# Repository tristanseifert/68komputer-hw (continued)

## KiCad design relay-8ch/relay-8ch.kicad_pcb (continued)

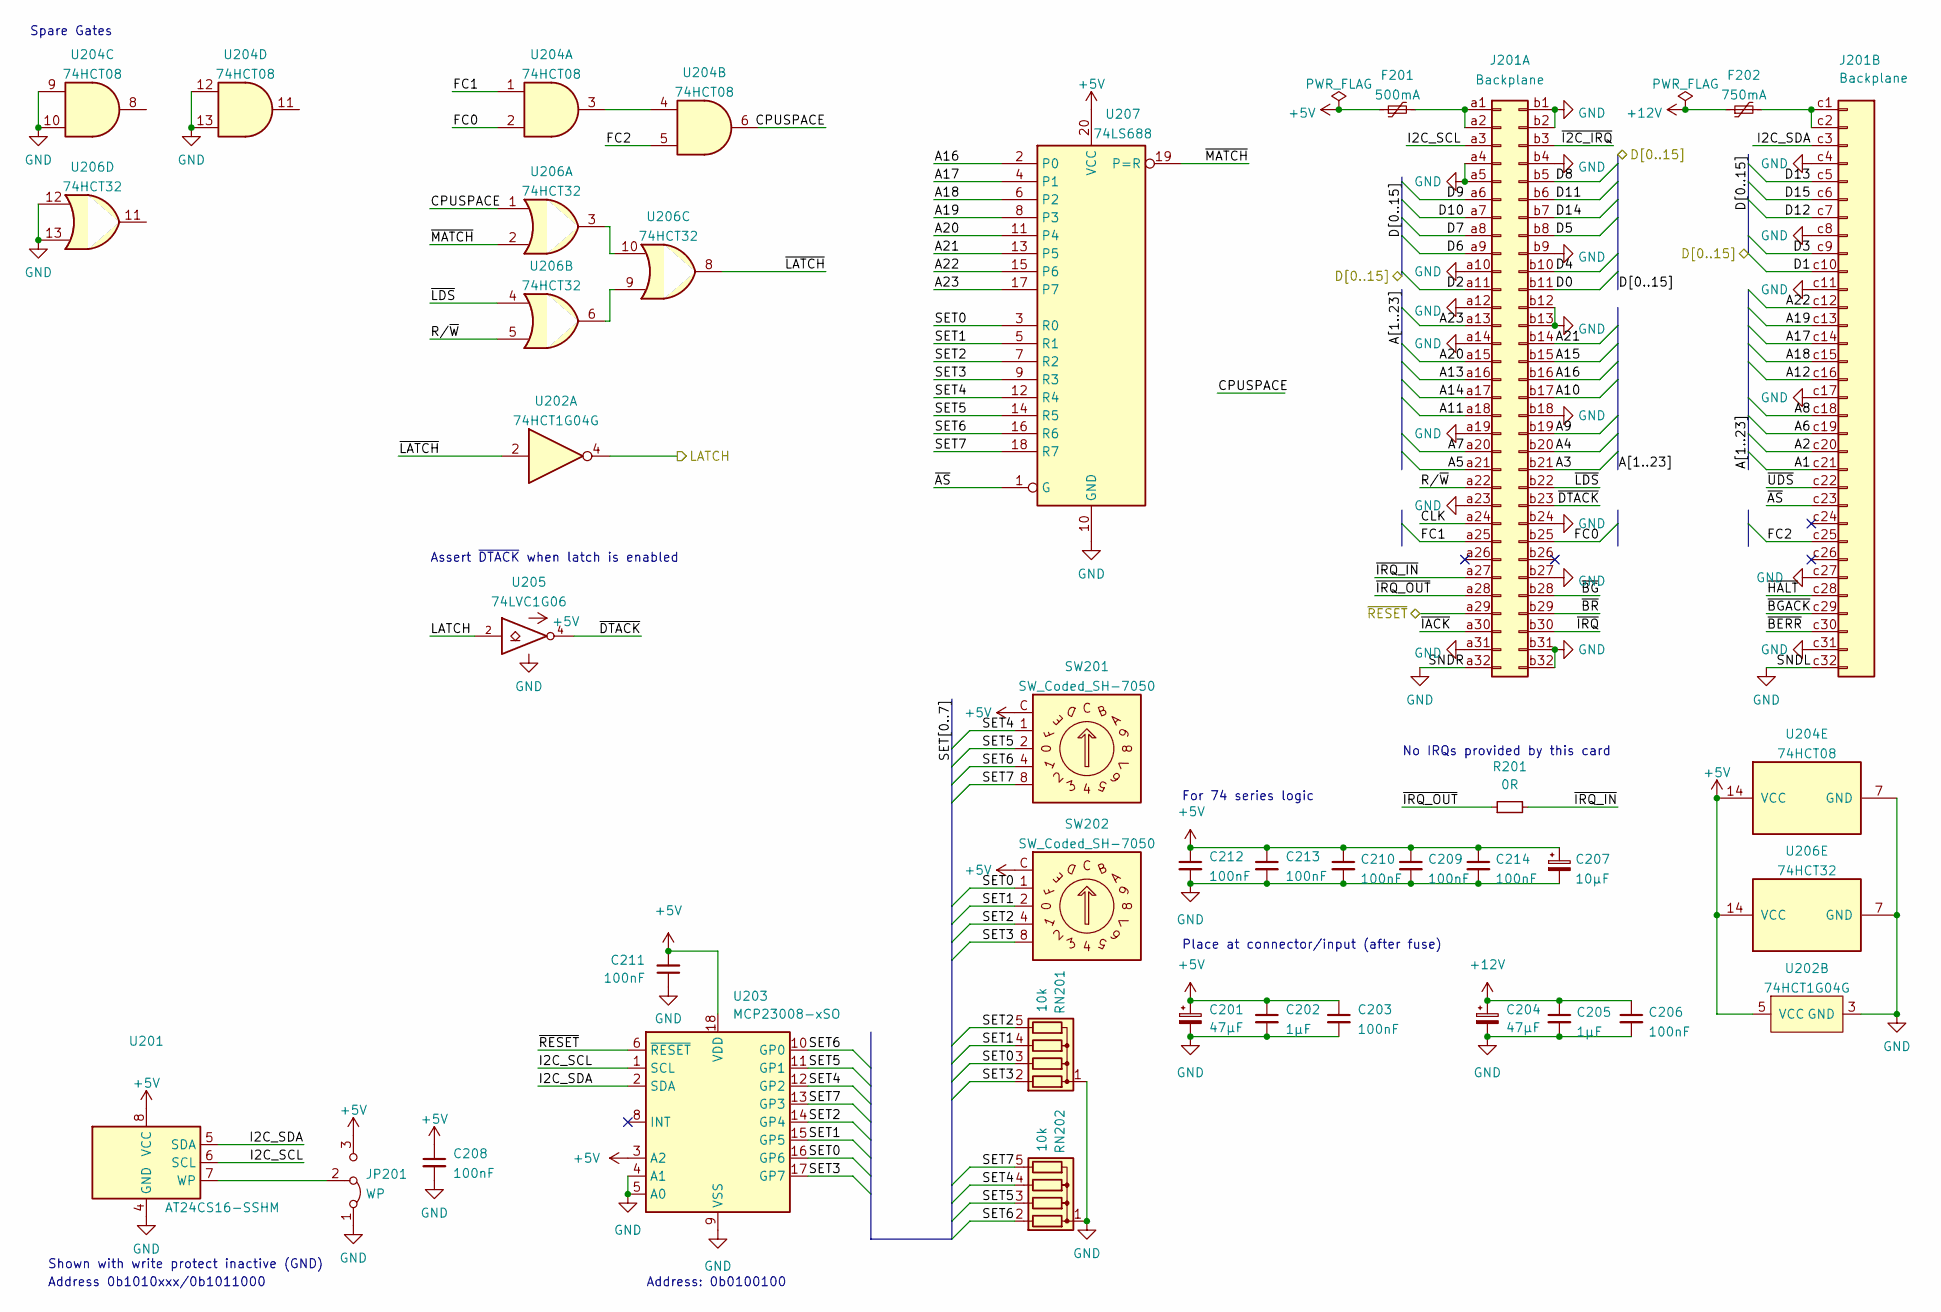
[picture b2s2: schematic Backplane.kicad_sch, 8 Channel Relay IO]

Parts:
C201, C204: 47µF; CP_Elec_6.3x5.7; MPN A768EB476M1ELAS042
C202, C205: 1µF; C_0805_2012Metric
C203, C206, C208, C209, C210, C211, C212, C213, C214: 100nF; C_0805_2012Metric
C207: 10µF; CP_EIA-3216-18_Kemet-A; MPN TAJA106K016RNJV
F201: 500mA; Fuse_1812_4532Metric; MPN 0ZCG0050FF2C
F202: 750mA; Fuse_1812_4532Metric; MPN 0ZCG0075FF2C
J201: Backplane; DIN41612_R_3x32_Male_Horizontal_THT
JP201: WP; SolderJumper-3_P1.3mm_Bridged2Bar12_Pad1.0x1.5mm
R201: 0R; R_0805_2012Metric; MPN RC0805JR-100RL
RN201, RN202: 10k; R_Array_SIP5; MPN 4605X-101-103LF
SW201, SW202: SW_Coded_SH-7050; Nidec_Copal_SH-7010C; MPN SH-7050MC
U201: AT24CS16-SSHM; SOIC-8_3.9x4.9mm_P1.27mm; MPN AT24CS32-SSHM-T
U202: 74HCT1G04G; SC-74-5_1.5x2.9mm_P0.95mm
U203: MCP23008-xSO; SOIC-18W_7.5x11.6mm_P1.27mm
U204: 74HCT08; SO-14_3.9x8.65mm_P1.27mm
U205: 74LVC1G06; SC-74-5_1.5x2.9mm_P0.95mm; MPN 74LVC1G06GV,125
U206: 74HCT32; SO-14_3.9x8.65mm_P1.27mm
U207: 74LS688; SOIC-20W_7.5x12.8mm_P1.27mm; MPN SN74LS688DWR

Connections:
+5V: C201.1, C202.1, C203.1, C207.1, C208.1, C209.1, C210.1, C211.2, C212.1, C213.1, C214.1, F201.1, JP201.3 (B), SW201.C, SW202.C, U201.8 (VCC), U202.5 (VCC), U203.3 (A2), U203.18 (VDD), U204.14 (VCC), U205.5 (VCC), U206.14 (VCC), U207.20 (VCC); also elsewhere on the board
+12V: C204.1, C205.1, C206.1, F202.1; also elsewhere on the board
/Backplane Connection/A1: J201.c21
/Backplane Connection/A2: J201.c20
/Backplane Connection/A3: J201.b21
/Backplane Connection/A4: J201.b20
/Backplane Connection/A5: J201.a21
/Backplane Connection/A6: J201.c19
/Backplane Connection/A7: J201.a20
/Backplane Connection/A8: J201.c18
/Backplane Connection/A9: J201.b19
/Backplane Connection/A10: J201.b17
/Backplane Connection/A11: J201.a18
/Backplane Connection/A12: J201.c16
/Backplane Connection/A13: J201.a16
/Backplane Connection/A14: J201.a17
/Backplane Connection/A15: J201.b15
/Backplane Connection/A16: J201.b16, U207.2 (P0)
/Backplane Connection/A17: J201.c14, U207.4 (P1)
/Backplane Connection/A18: J201.c15, U207.6 (P2)
/Backplane Connection/A19: J201.c13, U207.8 (P3)
/Backplane Connection/A20: J201.a15, U207.11 (P4)
/Backplane Connection/A21: J201.b14, U207.13 (P5)
/Backplane Connection/A22: J201.c12, U207.15 (P6)
/Backplane Connection/A23: J201.a13, U207.17 (P7)
/Backplane Connection/CLK: J201.a24
/Backplane Connection/CPUSPACE: U204.6, U206.1
/Backplane Connection/D8: J201.b5
/Backplane Connection/D9: J201.a6
/Backplane Connection/D10: J201.a7
/Backplane Connection/D11: J201.b6
/Backplane Connection/D12: J201.c7
/Backplane Connection/D13: J201.c5
/Backplane Connection/D14: J201.b7
/Backplane Connection/D15: J201.c6
/Backplane Connection/FC0: J201.b25, U204.2
/Backplane Connection/FC1: J201.a25, U204.1
/Backplane Connection/FC2: J201.c25, U204.5
/Backplane Connection/I2C_SCL: J201.a3, U201.6 (SCL), U203.1 (SCL)
/Backplane Connection/I2C_SDA: J201.c3, U201.5 (SDA), U203.2 (SDA)
/Backplane Connection/R/~W: J201.a22, U206.5
/Backplane Connection/SET0: RN201.3 (R2), SW202.1, U203.16 (GP6), U207.3 (R0)
/Backplane Connection/SET1: RN201.4 (R3), SW202.2, U203.15 (GP5), U207.5 (R1)
/Backplane Connection/SET2: RN201.5 (R4), SW202.4, U203.14 (GP4), U207.7 (R2)
/Backplane Connection/SET3: RN201.2 (R1), SW202.8, U203.17 (GP7), U207.9 (R3)
/Backplane Connection/SET4: RN202.4 (R3), SW201.1, U203.12 (GP2), U207.12 (R4)
/Backplane Connection/SET5: RN202.3 (R2), SW201.2, U203.11 (GP1), U207.14 (R5)
/Backplane Connection/SET6: RN202.2 (R1), SW201.4, U203.10 (GP0), U207.16 (R6)
/Backplane Connection/SET7: RN202.5 (R4), SW201.8, U203.13 (GP3), U207.18 (R7)
/Backplane Connection/~AS: J201.c23, U207.1 (G)
/Backplane Connection/~BERR: J201.c30
/Backplane Connection/~BGACK: J201.c29
/Backplane Connection/~BG: J201.b28
/Backplane Connection/~BR: J201.b29
/Backplane Connection/~DTACK: J201.b23, U205.4
/Backplane Connection/~HALT: J201.c28
/Backplane Connection/~I2C_IRQ: J201.b3
/Backplane Connection/~IACK: J201.a30
/Backplane Connection/~IRQ_IN: J201.a27, R201.2
/Backplane Connection/~IRQ_OUT: J201.a28, R201.1
/Backplane Connection/~IRQ: J201.b30
/Backplane Connection/~LATCH: U202.2, U206.8
/Backplane Connection/~LDS: J201.b22, U206.4
/Backplane Connection/~MATCH: U206.2, U207.19 (P=R)
/Backplane Connection/~RESET: J201.a29, U203.6 (~RESET)
/Backplane Connection/~UDS: J201.c22
/D0: J201.b11; also elsewhere on the board
/D1: J201.c10; also elsewhere on the board
/D2: J201.a11; also elsewhere on the board
/D3: J201.c9; also elsewhere on the board
/D4: J201.b10; also elsewhere on the board
/D5: J201.b8; also elsewhere on the board
/D6: J201.a9; also elsewhere on the board
/D7: J201.a8; also elsewhere on the board
/LATCH: U202.4, U205.2; also elsewhere on the board
GND: C201.2, C202.2, C203.2, C204.2, C205.2, C206.2, C207.2, C208.2, C209.2, C210.2, C211.1, C212.2, C213.2, C214.2, J201.a4, J201.a5, J201.a10, J201.a12, J201.a14, J201.a19, J201.a23, J201.a31, J201.a32, J201.b1, J201.b2, J201.b4, J201.b9, J201.b12, J201.b13, J201.b18, J201.b24, J201.b27, J201.b31, J201.b32, J201.c4, J201.c8, J201.c11, J201.c17, J201.c27, J201.c31, J201.c32, JP201.1 (A), RN201.1 (common), RN202.1 (common), U201.4 (GND), U202.3 (GND), U203.4 (A1), U203.5 (A0), U203.9 (VSS), U204.7 (GND), U204.9, U204.10, U204.12, U204.13, U205.3 (GND), U206.7 (GND), U206.12, U206.13, U207.10 (GND); also elsewhere on the board
unnamed: F201.2, J201.a1, J201.a2
unnamed: F202.2, J201.c1, J201.c2
unnamed: JP201.2 (C), U201.7 (WP)
unnamed: U204.3, U204.4
unnamed: U206.6, U206.9
unnamed: U206.3, U206.10

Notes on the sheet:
Shown with write protect inactive (GND)
Place at connector/input (after fuse)
No IRQs provided by this card
Spare Gates
Assert ~{DTACK} when latch is enabled
For 74 series logic
Address 0b1010xxx/0b1011000
Address: 0b0100100

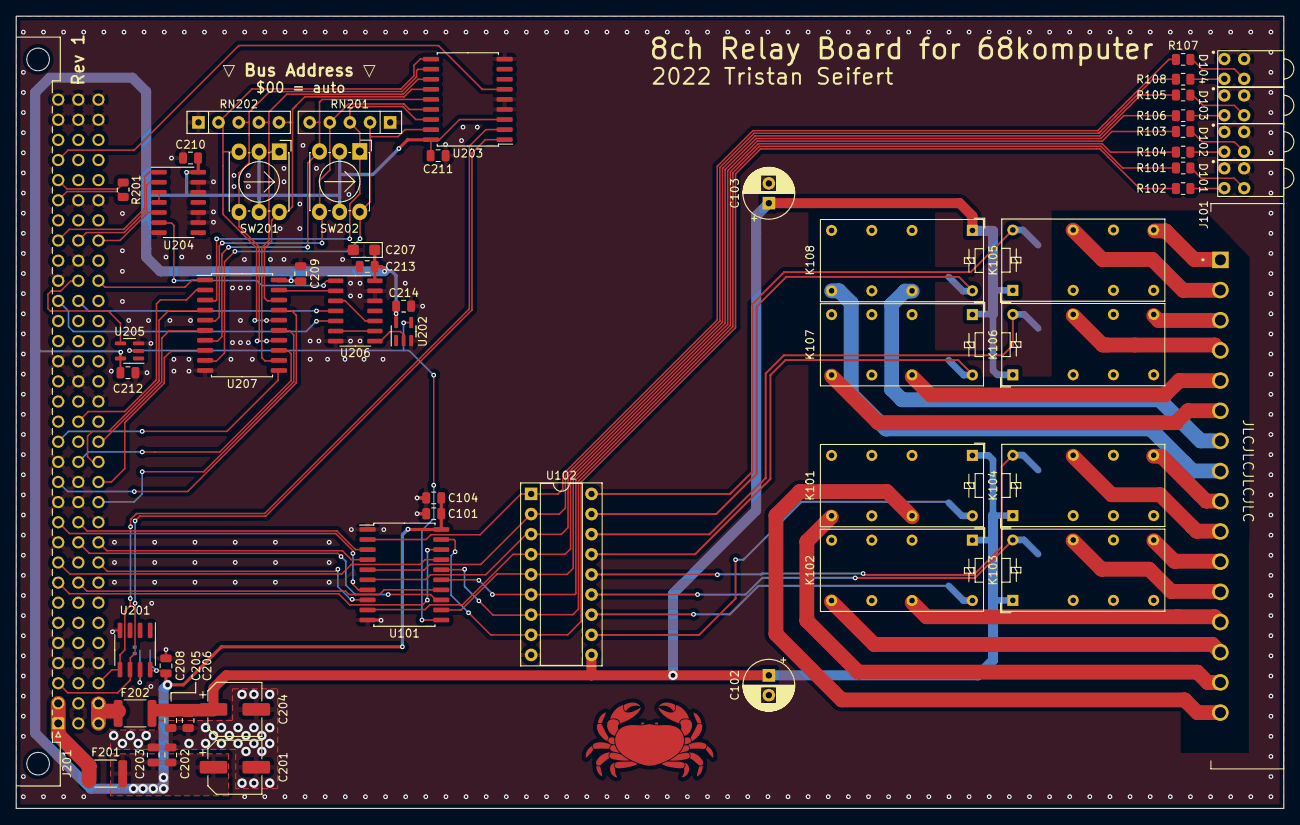
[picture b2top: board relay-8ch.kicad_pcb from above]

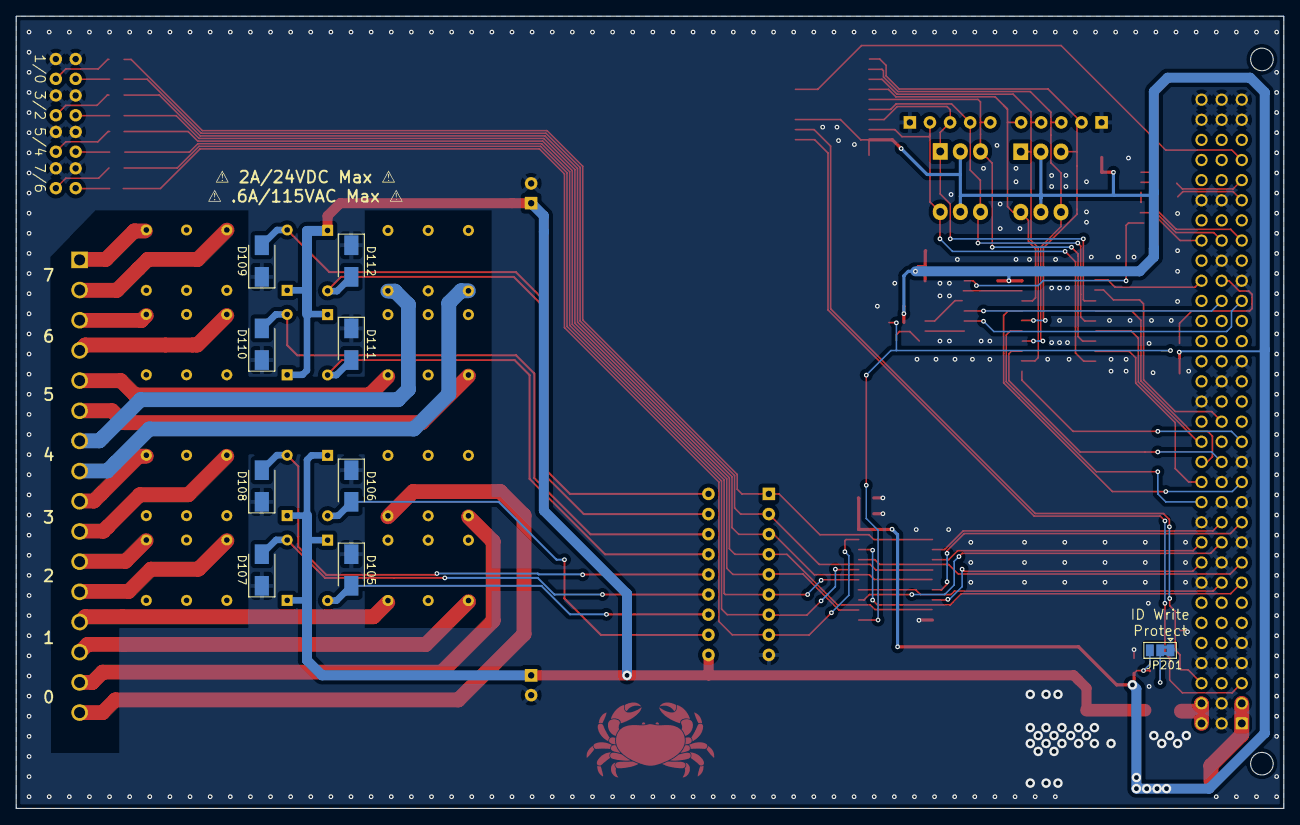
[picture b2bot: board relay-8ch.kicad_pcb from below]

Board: 2 copper layers, 160.0 x 100.0 mm, 65 parts (9 on the bottom side), 89 nets.

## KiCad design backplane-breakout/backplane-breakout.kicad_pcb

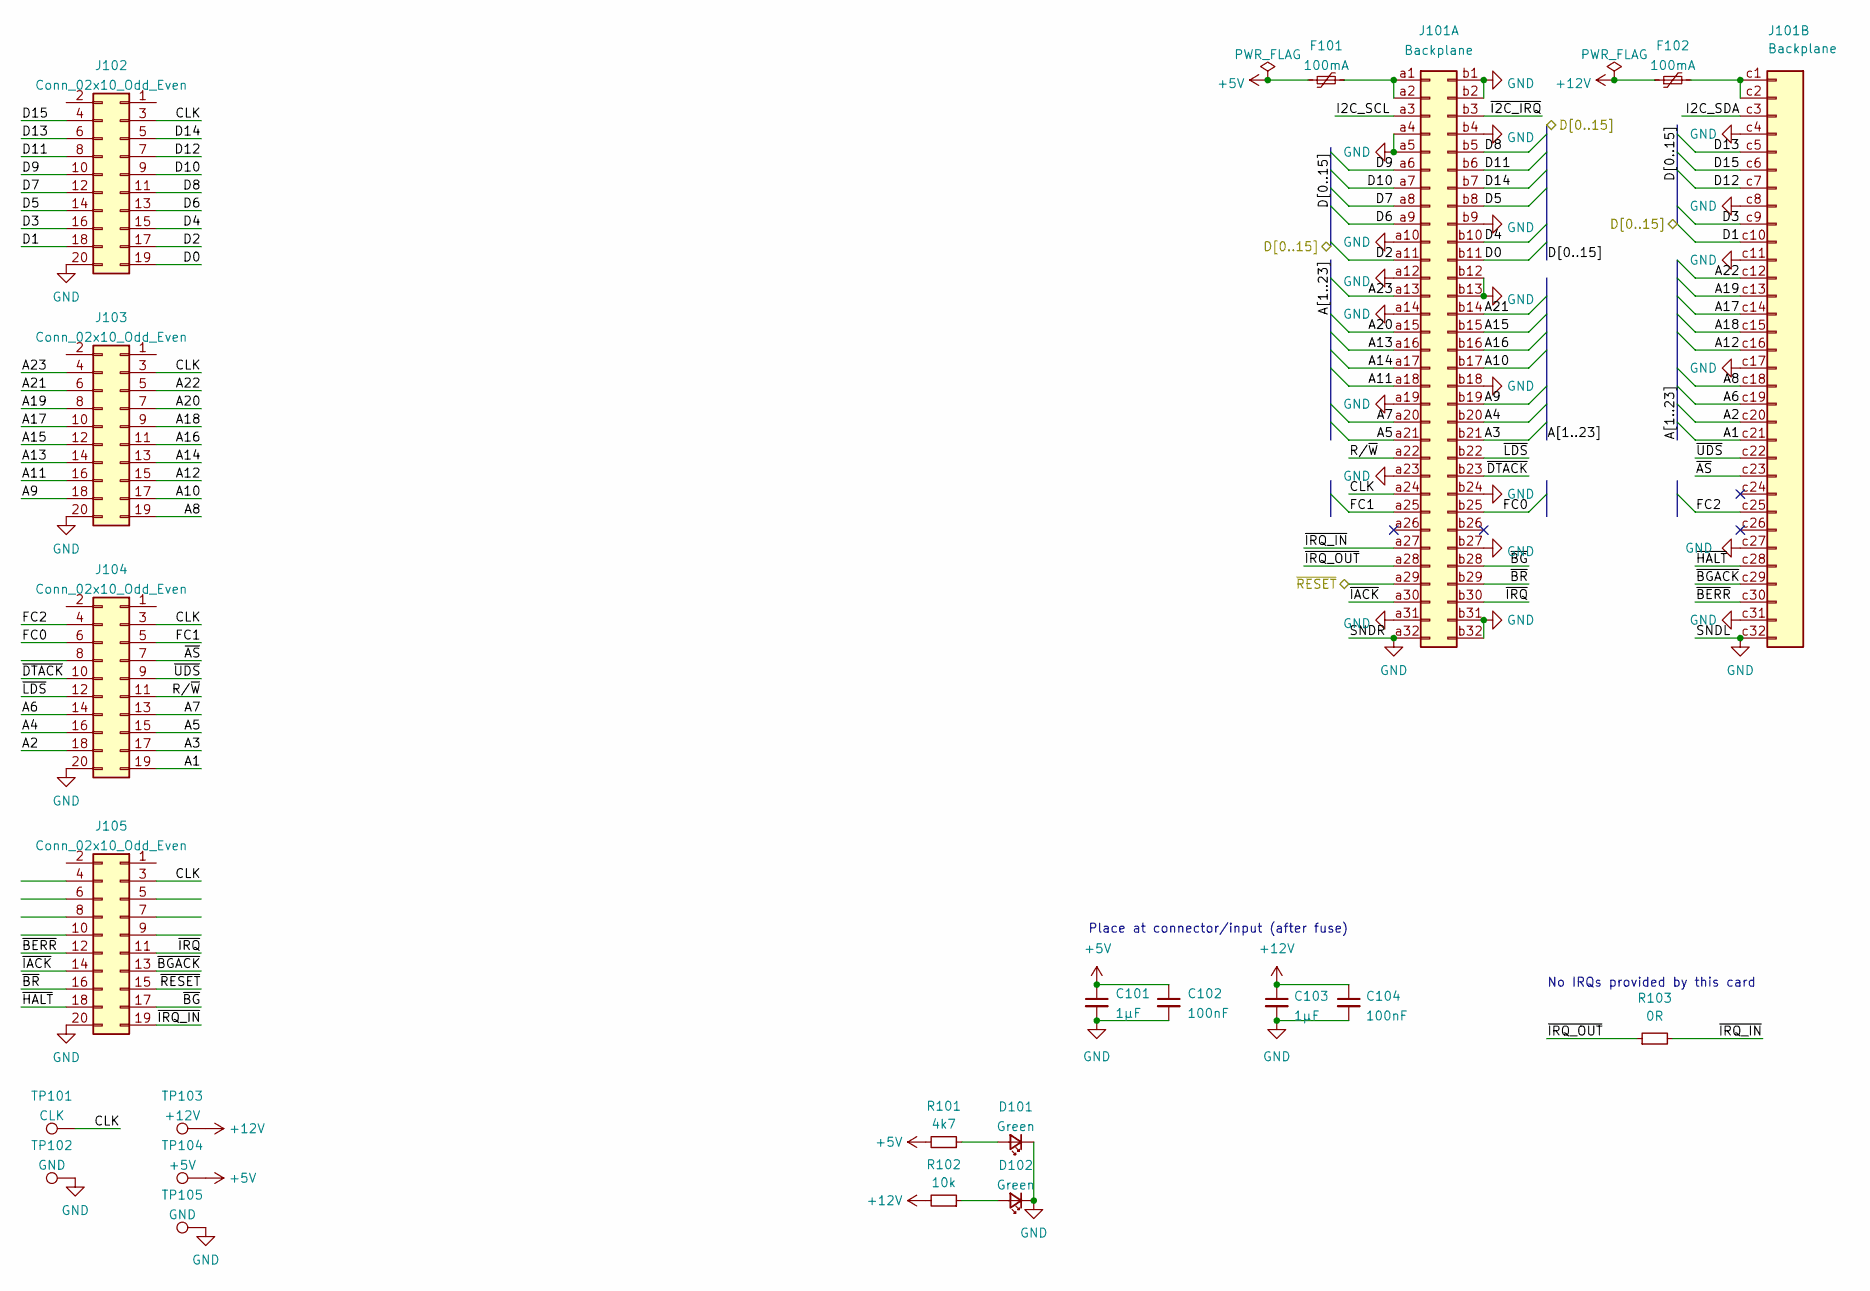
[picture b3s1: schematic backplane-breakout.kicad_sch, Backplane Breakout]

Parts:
C101, C103: 1µF; C_0805_2012Metric
C102, C104: 100nF; C_0805_2012Metric
D101, D102: Green; LED_0805_2012Metric
F101, F102: 100mA; Fuse_1812_4532Metric; MPN PTS181230V010
J101: Backplane; DIN41612_R_3x32_Male_Horizontal_THT; MPN 86093967113H55ELF
J102, J103, J104, J105: Conn_02x10_Odd_Even; Shrouded_PinHeader_2x10_P2.54mm_Vertical
R101: 4k7; R_0805_2012Metric
R102: 10k; R_0805_2012Metric
R103: 0R; R_0805_2012Metric; MPN RC0805JR-100RL
TP101: CLK; TestPoint_Keystone_5000-5004_Miniature
TP102, TP105: GND; TestPoint_Keystone_5000-5004_Miniature
TP103: +12V; TestPoint_Keystone_5000-5004_Miniature
TP104: +5V; TestPoint_Keystone_5000-5004_Miniature

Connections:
+5V: C101.1, C102.1, F101.1, R101.2, TP104.1
+12V: C103.1, C104.1, F102.1, R102.2, TP103.1
/A1: J101.c21, J104.19
/A2: J101.c20, J104.18
/A3: J101.b21, J104.17
/A4: J101.b20, J104.16
/A5: J101.a21, J104.15
/A6: J101.c19, J104.14
/A7: J101.a20, J104.13
/A8: J101.c18, J103.19
/A9: J101.b19, J103.18
/A10: J101.b17, J103.17
/A11: J101.a18, J103.16
/A12: J101.c16, J103.15
/A13: J101.a16, J103.14
/A14: J101.a17, J103.13
/A15: J101.b15, J103.12
/A16: J101.b16, J103.11
/A17: J101.c14, J103.10
/A18: J101.c15, J103.9
/A19: J101.c13, J103.8
/A20: J101.a15, J103.7
/A21: J101.b14, J103.6
/A22: J101.c12, J103.5
/A23: J101.a13, J103.4
/CLK: J101.a24, J102.3, J103.3, J104.3, J105.3, TP101.1
/D0: J101.b11, J102.19
/D1: J101.c10, J102.18
/D2: J101.a11, J102.17
/D3: J101.c9, J102.16
/D4: J101.b10, J102.15
/D5: J101.b8, J102.14
/D6: J101.a9, J102.13
/D7: J101.a8, J102.12
/D8: J101.b5, J102.11
/D9: J101.a6, J102.10
/D10: J101.a7, J102.9
/D11: J101.b6, J102.8
/D12: J101.c7, J102.7
/D13: J101.c5, J102.6
/D14: J101.b7, J102.5
/D15: J101.c6, J102.4
/FC0: J101.b25, J104.6
/FC1: J101.a25, J104.5
/FC2: J101.c25, J104.4
/I2C_SCL: J101.a3
/I2C_SDA: J101.c3
/R/~W: J101.a22, J104.11
/~AS: J101.c23, J104.7
/~BERR: J101.c30, J105.12
/~BGACK: J101.c29, J105.13
/~BG: J101.b28, J105.17
/~BR: J101.b29, J105.16
/~DTACK: J101.b23, J104.10
/~HALT: J101.c28, J105.18
/~I2C_IRQ: J101.b3
/~IACK: J101.a30, J105.14
/~IRQ_IN: J101.a27, J105.19, R103.2
/~IRQ_OUT: J101.a28, R103.1
/~IRQ: J101.b30, J105.11
/~LDS: J101.b22, J104.12
/~RESET: J101.a29, J105.15
/~UDS: J101.c22, J104.9
GND: C101.2, C102.2, C103.2, C104.2, D101.1 (K), D102.1 (K), J101.a4, J101.a5, J101.a10, J101.a12, J101.a14, J101.a19, J101.a23, J101.a31, J101.a32, J101.b1, J101.b2, J101.b4, J101.b9, J101.b12, J101.b13, J101.b18, J101.b24, J101.b27, J101.b31, J101.b32, J101.c4, J101.c8, J101.c11, J101.c17, J101.c27, J101.c31, J101.c32, J102.20, J103.20, J104.20, J105.20, TP102.1, TP105.1
unnamed: D101.2 (A), R101.1
unnamed: D102.2 (A), R102.1
unnamed: F101.2, J101.a1, J101.a2
unnamed: F102.2, J101.c1, J101.c2

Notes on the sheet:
No IRQs provided by this card
Place at connector/input (after fuse)

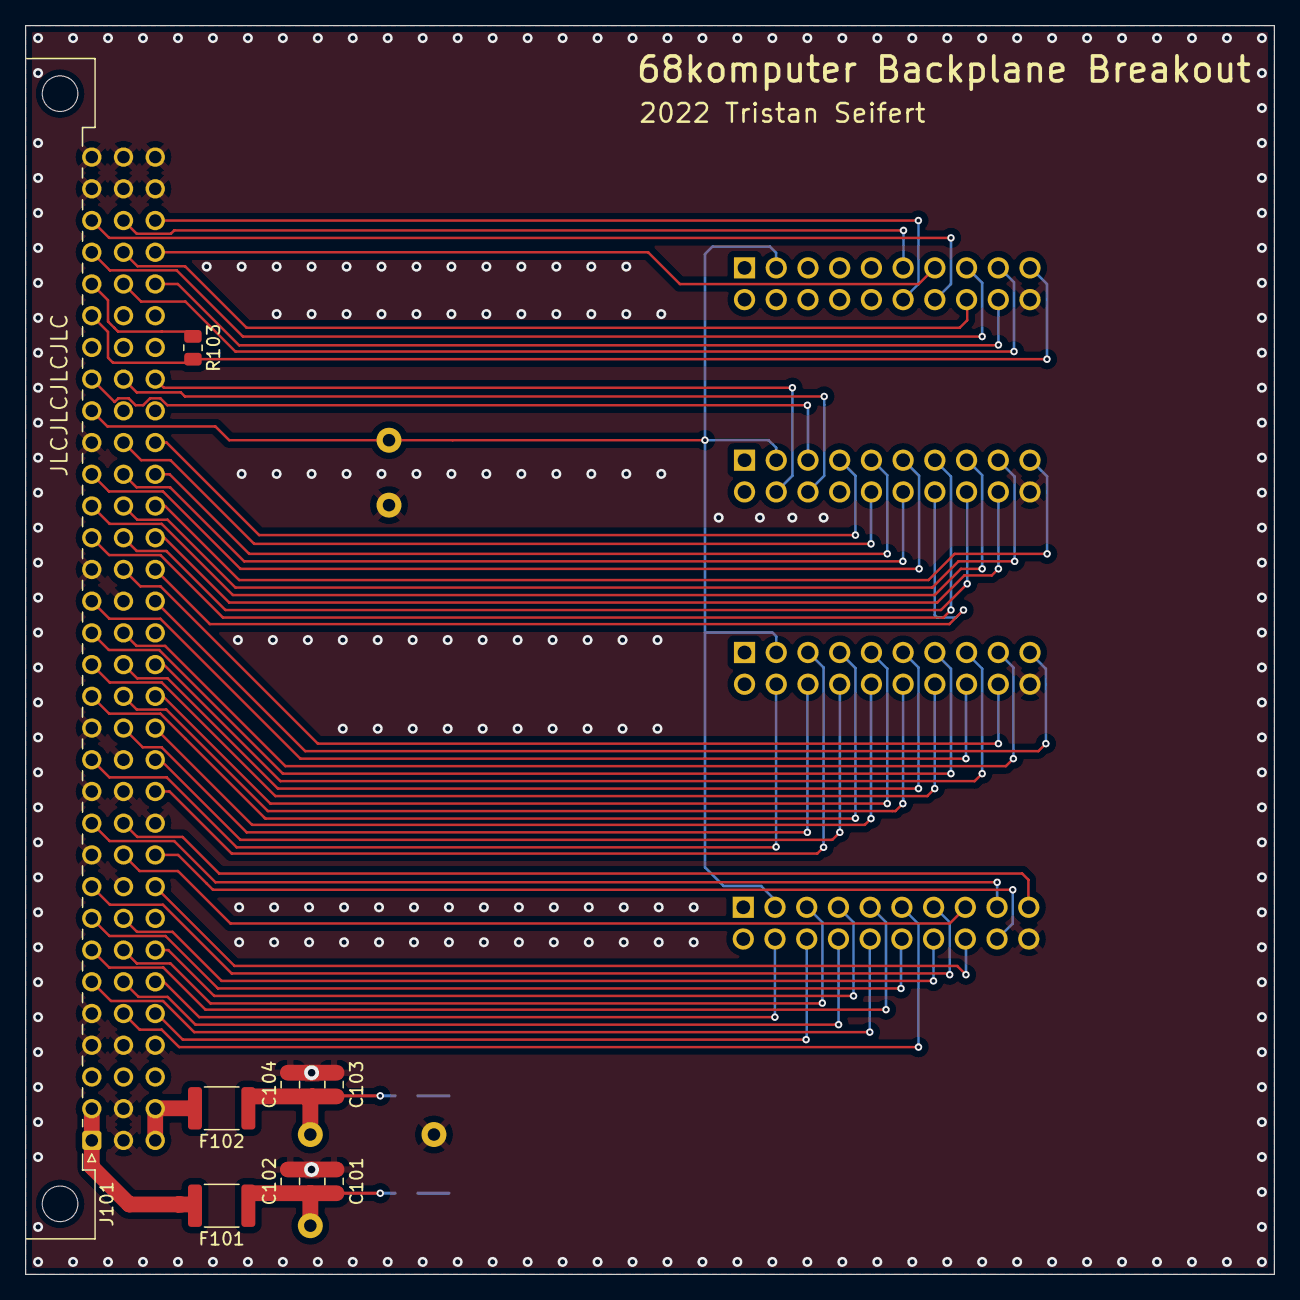
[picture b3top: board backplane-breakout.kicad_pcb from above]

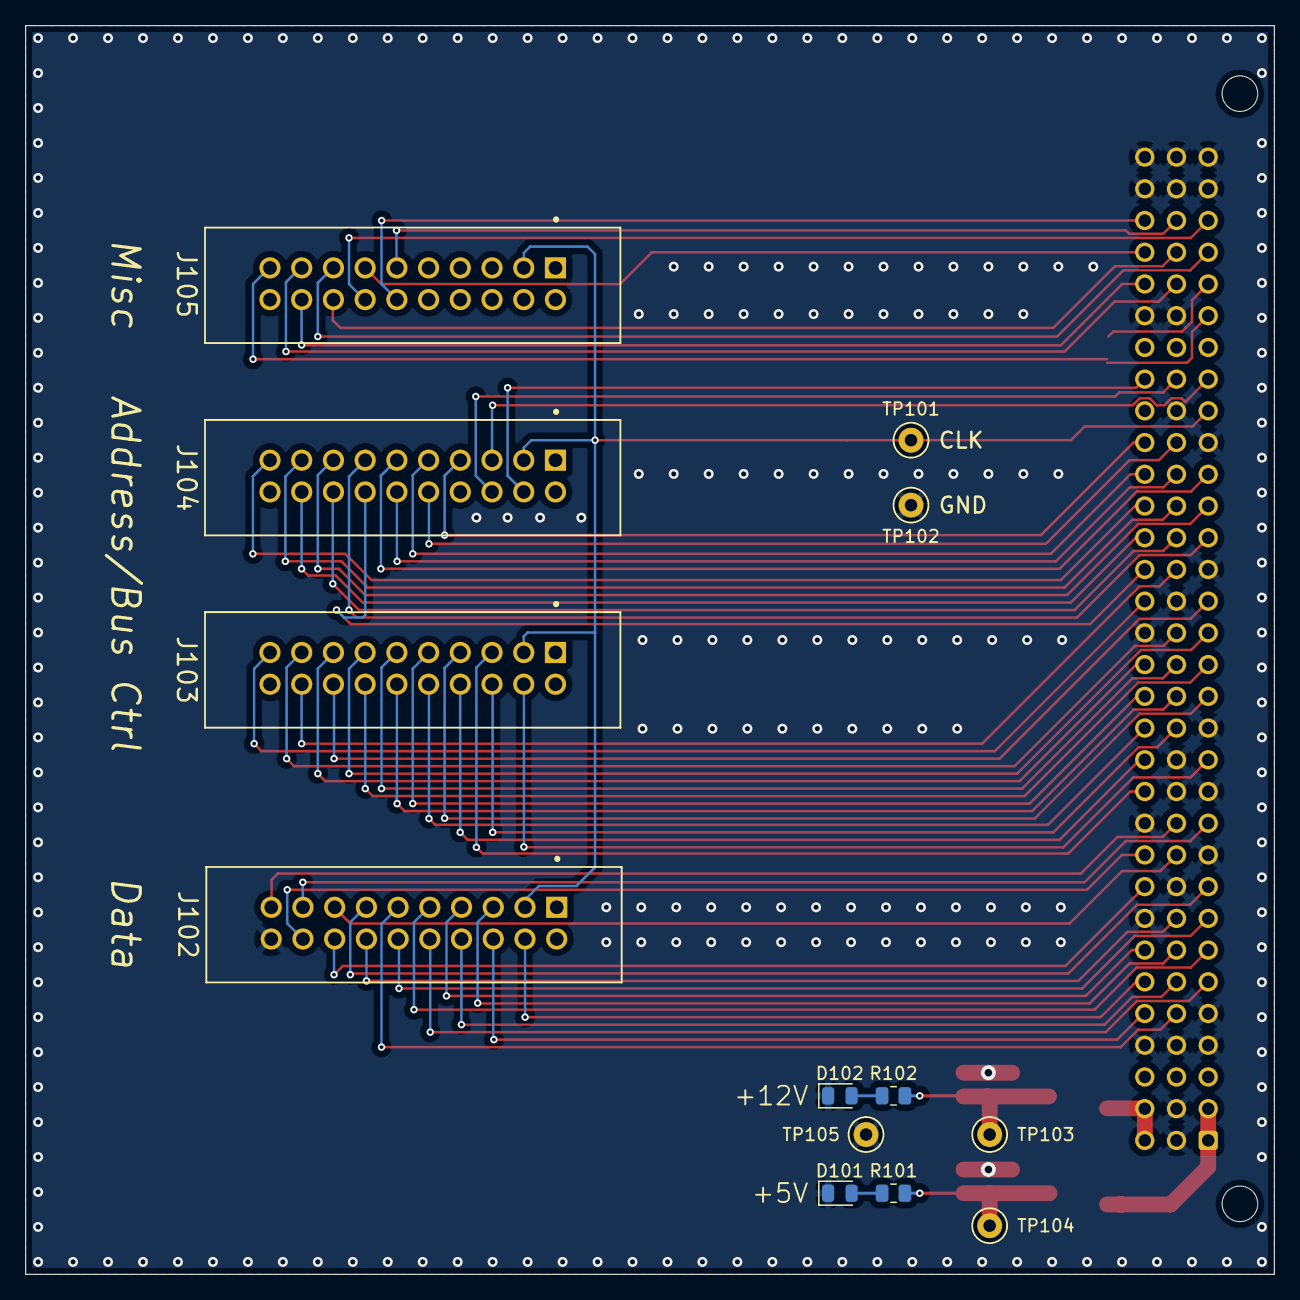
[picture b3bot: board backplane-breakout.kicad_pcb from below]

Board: 2 copper layers, 100.0 x 100.0 mm, 21 parts (13 on the bottom side), 65 nets.

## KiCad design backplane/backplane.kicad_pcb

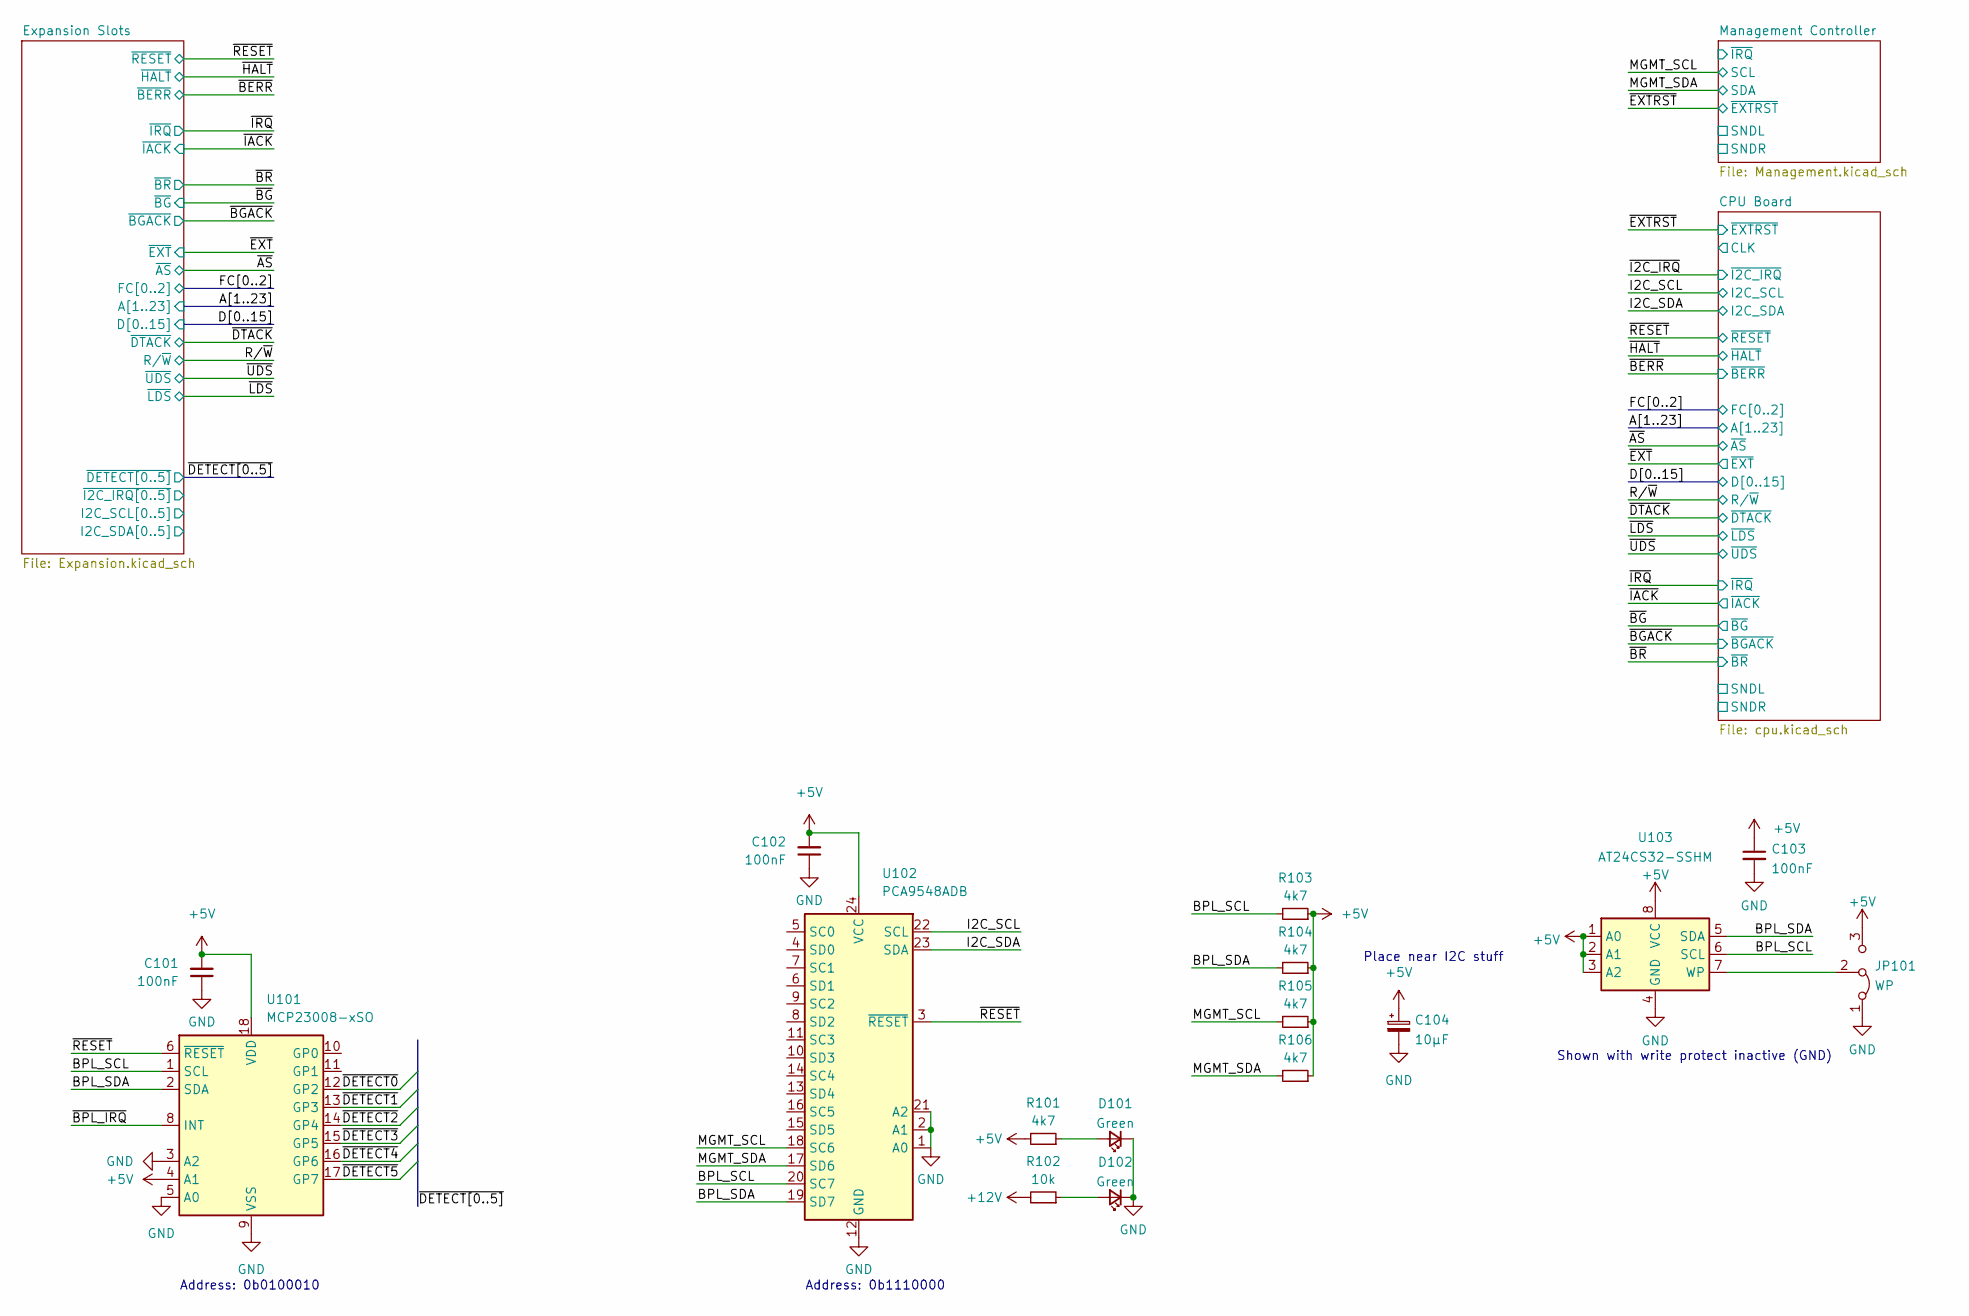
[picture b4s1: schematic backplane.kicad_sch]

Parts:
C101, C102, C103: 100nF; C_0805_2012Metric
C104: 10µF; CP_EIA-3216-18_Kemet-A; MPN TAJA106K016RNJV
D101, D102: Green; LED_0805_2012Metric
JP101: WP; SolderJumper-3_P1.3mm_Bridged2Bar12_Pad1.0x1.5mm
R101, R103, R104, R105, R106: 4k7; R_0805_2012Metric
R102: 10k; R_0805_2012Metric
U101: MCP23008-xSO; SOIC-18W_7.5x11.6mm_P1.27mm
U102: PCA9548ADB; SSOP-24_5.3x8.2mm_P0.65mm
U103: AT24CS32-SSHM; SOIC-8_3.9x4.9mm_P1.27mm; MPN AT24CS32-SSHM-T

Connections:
+5V: C101.2, C102.2, C103.1, C104.1, JP101.3 (B), R101.2, R103.1, R104.1, R105.1, R106.1, U101.4 (A1), U101.18 (VDD), U102.24 (VCC), U103.1 (A0), U103.2 (A1), U103.3 (A2), U103.8 (VCC); also elsewhere on the board
+12V: R102.2; also elsewhere on the board
/BPL_SCL: R103.2, U101.1 (SCL), U102.20 (SC7), U103.6 (SCL)
/BPL_SDA: R104.2, U101.2 (SDA), U102.19 (SD7), U103.5 (SDA)
/I2C_SCL: U102.22 (SCL); also elsewhere on the board
/I2C_SDA: U102.23 (SDA); also elsewhere on the board
/MGMT_SCL: R105.2, U102.18 (SC6); also elsewhere on the board
/MGMT_SDA: R106.2, U102.17 (SD6); also elsewhere on the board
/~BPL_IRQ: U101.8 (INT)
/~DETECT0: U101.12 (GP2); also elsewhere on the board
/~DETECT1: U101.13 (GP3); also elsewhere on the board
/~DETECT2: U101.14 (GP4); also elsewhere on the board
/~DETECT3: U101.15 (GP5); also elsewhere on the board
/~DETECT4: U101.16 (GP6); also elsewhere on the board
/~DETECT5: U101.17 (GP7); also elsewhere on the board
/~RESET: U101.6 (~RESET), U102.3 (~RESET); also elsewhere on the board
GND: C101.1, C102.1, C103.2, C104.2, D101.1 (K), D102.1 (K), JP101.1 (A), U101.3 (A2), U101.5 (A0), U101.9 (VSS), U102.1 (A0), U102.2 (A1), U102.12 (GND), U102.21 (A2), U103.4 (GND); also elsewhere on the board
unnamed: D101.2 (A), R101.1
unnamed: D102.2 (A), R102.1
unnamed: JP101.2 (C), U103.7 (WP)

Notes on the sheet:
Address: 0b1110000
Address: 0b0100010
Place near I2C stuff
Shown with write protect inactive (GND)

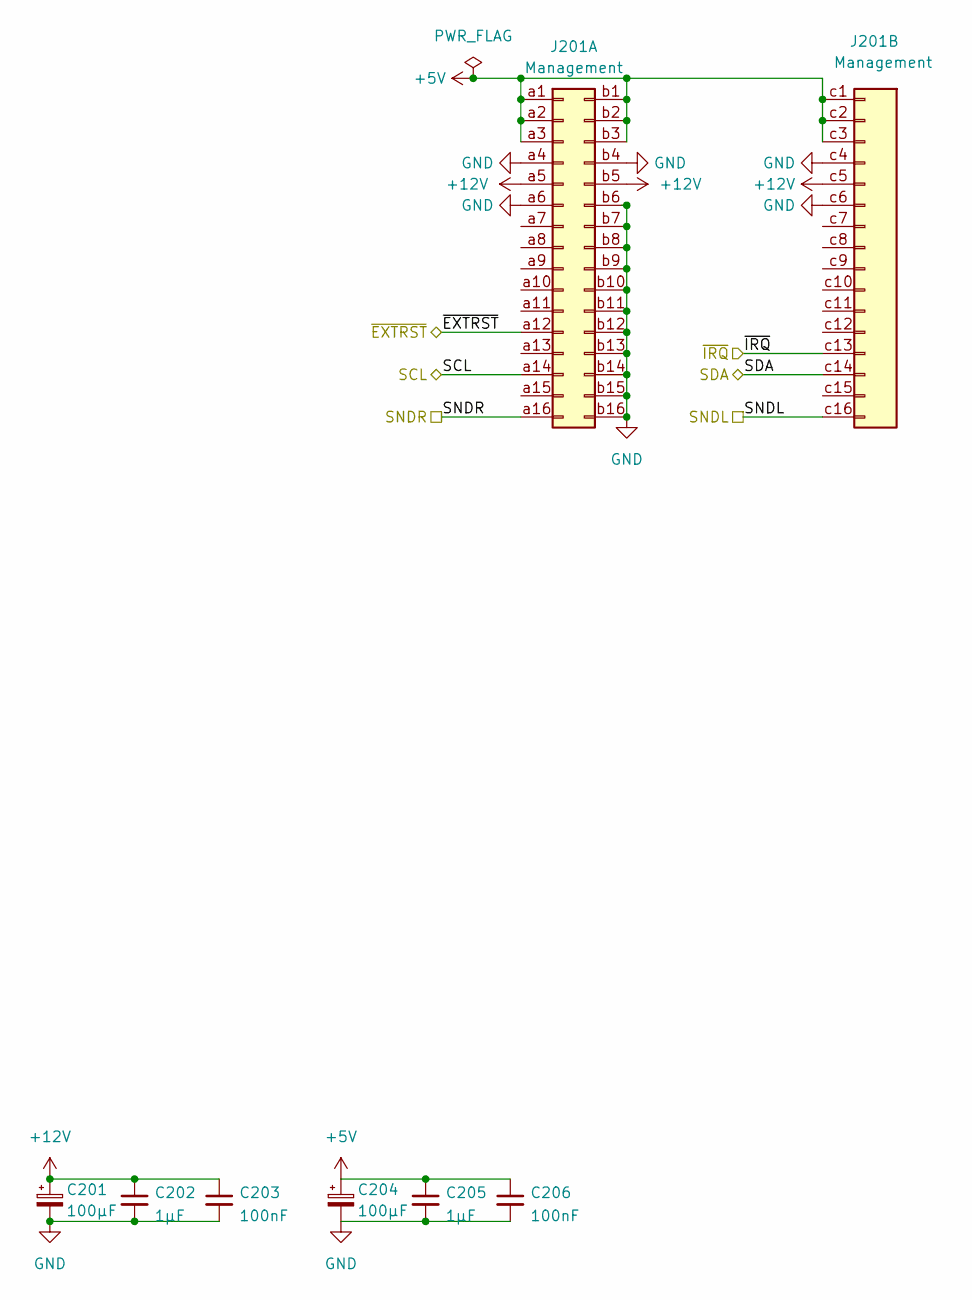
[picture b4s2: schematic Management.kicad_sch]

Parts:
C201: 100µF; CP_Radial_D8.0mm_P3.50mm; MPN A750KK107M1EAAE040
C202, C205: 1µF; C_0805_2012Metric
C203, C206: 100nF; C_0805_2012Metric
C204: 100µF; CP_Radial_D5.0mm_P2.00mm; MPN A750BK107M1AAAE024
J201: Management; DIN41612_C2_3x16_Female_Vertical_THT

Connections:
+5V: C204.1, C205.1, C206.1, J201.a1, J201.a2, J201.a3, J201.b1, J201.b2, J201.b3, J201.c1, J201.c2, J201.c3; also elsewhere on the board
+12V: C201.1, C202.1, C203.1, J201.a5, J201.b5, J201.c5; also elsewhere on the board
/MGMT_SCL: J201.a14; also elsewhere on the board
/MGMT_SDA: J201.c14; also elsewhere on the board
/Management Controller/SNDL: J201.c16
/Management Controller/SNDR: J201.a16
/Management Controller/~IRQ: J201.c13
/~EXTRST: J201.a12; also elsewhere on the board
GND: C201.2, C202.2, C203.2, C204.2, C205.2, C206.2, J201.a4, J201.a6, J201.b4, J201.b6, J201.b7, J201.b8, J201.b9, J201.b10, J201.b11, J201.b12, J201.b13, J201.b14, J201.b15, J201.b16, J201.c4, J201.c6; also elsewhere on the board
